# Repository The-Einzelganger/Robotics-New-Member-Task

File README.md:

# Robotics-New-Member-Task
Robotics_Disivion

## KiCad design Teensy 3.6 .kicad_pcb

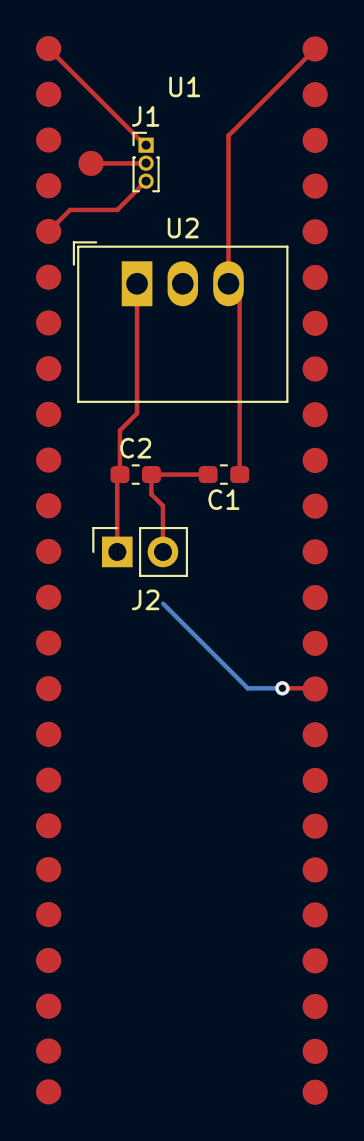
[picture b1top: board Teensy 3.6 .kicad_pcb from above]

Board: 2 copper layers, 6 parts (0 on the bottom side), 6 nets.

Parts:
C1, C2: C; C_0603_1608Metric_Pad1.05x0.95mm_HandSolder
J1: Servo Control Connector; PinHeader_1x03_P1.00mm_Vertical
J2: Input Power; PinSocket_1x02_P2.54mm_Vertical
U1: Teensy3.6
U2: R-78B5.0-2.0; Converter_DCDC_RECOM_R-78B-2.0_THT

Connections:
GND: C1.2, C2.2, J2.2, U1.GND2, U2.2
unnamed: C1.1, U1.Vin, U2.3
unnamed: C2.1, J2.1, U2.1
unnamed: J1.1, U1.GND1
unnamed: J1.2, U1.5V
unnamed: J1.3, U1.3
